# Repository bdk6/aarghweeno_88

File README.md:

# aarghweeno_88
An Arduino compatible prototyping board

Short story: add prototyping area to Arduino compatible AVR development board.

I have been a fan of the AVR processors for a long time.  My first project with them was in 2006.  The Arduino came along later and it is a neat system, making it very easy to get started.  When I say "Arduino" I mean AVR based ones.  If I should refer to some other, I'll specify.  

Now you can get an Aruino Nano clone for less than $5 US all over the web.  But one thing that has often bothered me about all the standard Arduino boards is that they don't have onbaord prototyping areas.  This little project aims to fix that.

The board is 3.9 x 3.9 inches, just under the 100 x 100 mm size of JLCPCBs cheapest PC board service.  About 1 1/2 inch along the "top" edge holds the AVR, regulator, programming header, and associated components.  The rest of the board is taken up with a prototyping area of holes on 0.1" centers arranged in groups of threes and long rows of bus connections.  There are also four mounting holes, another thing absent from standard Arduinos.  The idea is you can build an entire project on a single board without all those "dupont" (I hate that name) wires and whatnot crap going from board to board.

The one thing I left off that I agonized over was a USB interface or any type of serial port circuit.  Many of my projects don't need either and I generally prefer to use an AVR programmer to flash the chip.  If you really need/want a USB interface you can add it in the proto area.  You might need an SMD to DIP adapter or maybe just buy a USB to 5V serial module with 0.1" header pins.

You are welcome to use this board for any purpose, personal or commercial, as long as you leave the copyright notice in place.  I would like to know about any projects you build with it or comments in general.  If you make enough money selling it to hire Bill Gates and Jeff Bezos as your house boys, I wouldn't mind if you slipped me a mil or two.

20220807   First set of boards
I got the first boards back from JLCPCB on Thursday.  Friday morning I started soldering one up.  After replacing the LED that I soldered in backward, everthing seems to be working fine.  A bit more testing to do, but so far, so good.

Today I cleaned up some minor flaws and I'm releasing version 1.1.  Changed to value of C3 (to 0.1 uF from 0.33 uF) and cleaned up some silkscreen.  No substantive changes.  I plan to run a set of these once I've tested the first one more.

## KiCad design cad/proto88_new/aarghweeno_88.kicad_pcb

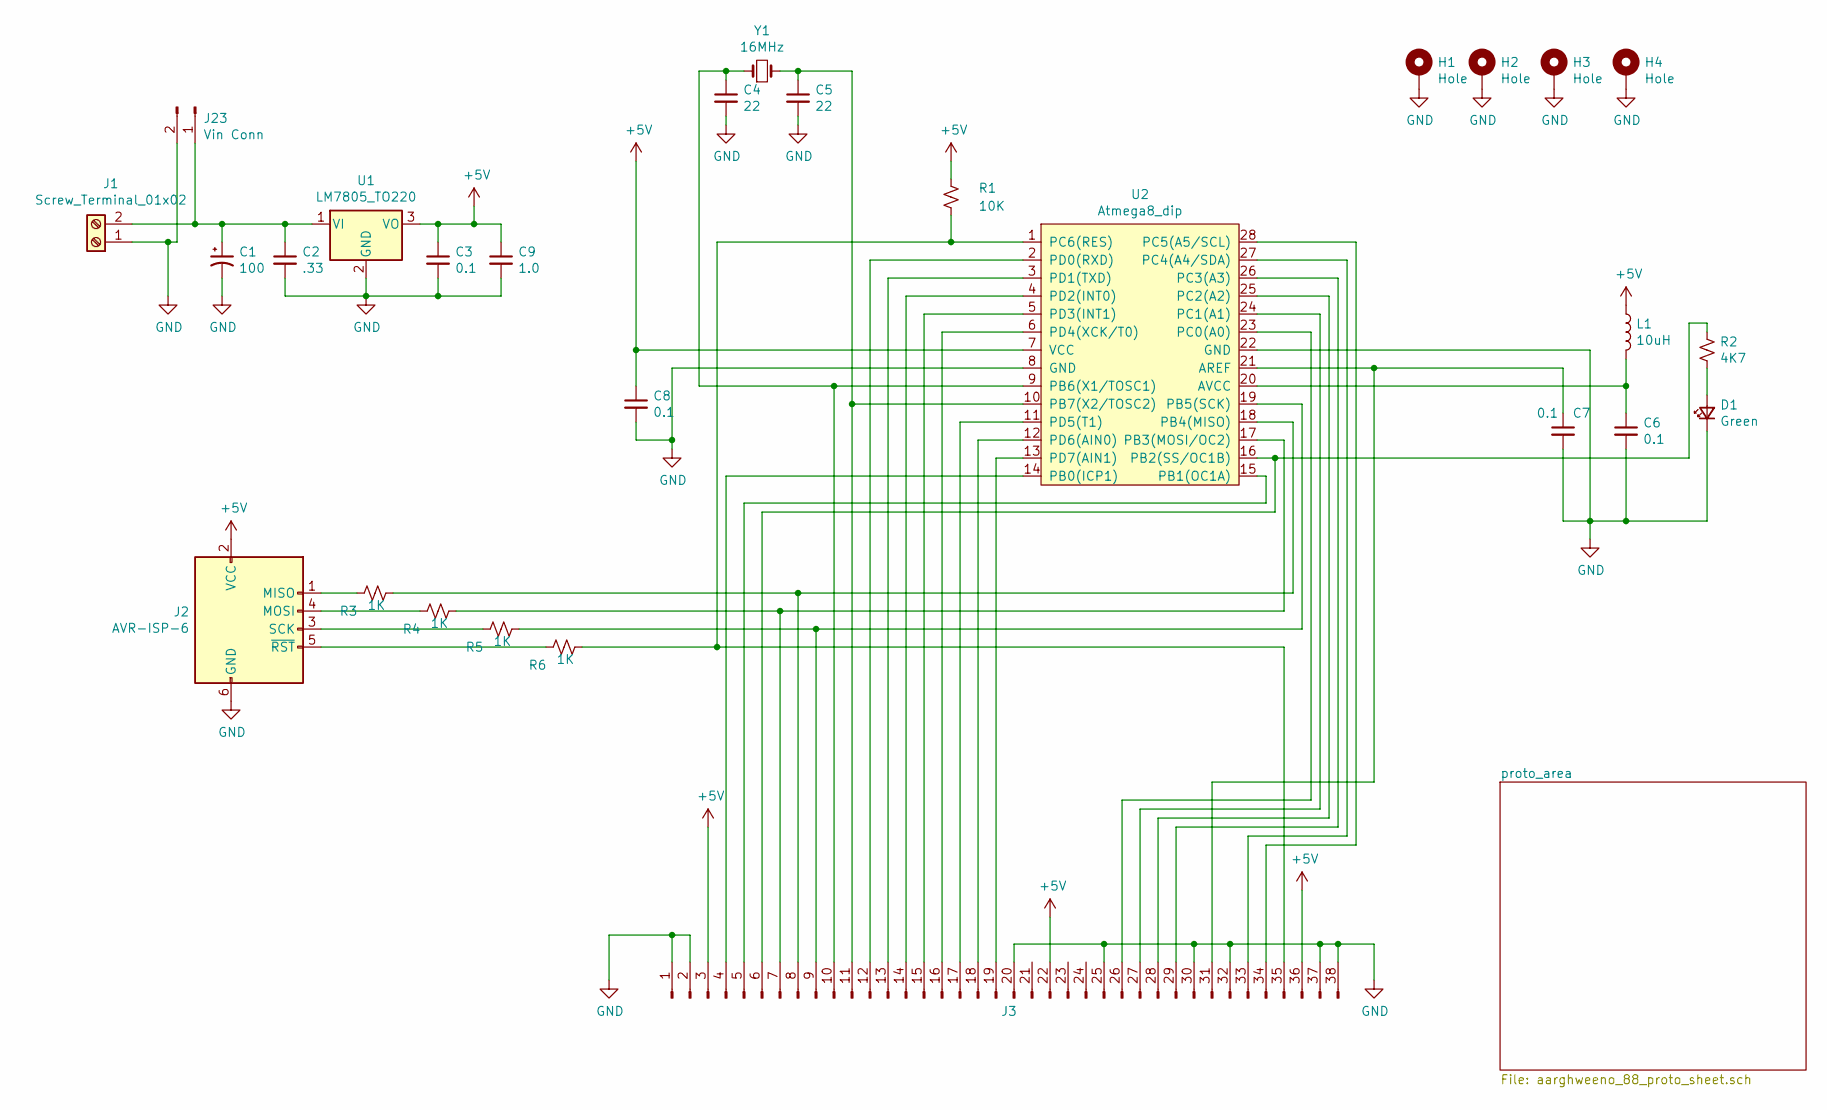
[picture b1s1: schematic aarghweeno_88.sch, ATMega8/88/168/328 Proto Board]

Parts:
C1: 100; CP_Radial_D8.0mm_P5.00mm
C2: .33; C_Disc_D5.0mm_W2.5mm_P5.00mm
C3, C6, C7, C8: 0.1; C_Disc_D5.0mm_W2.5mm_P5.00mm
C4, C5: 22; C_Disc_D5.0mm_W2.5mm_P5.00mm
C9: 1.0; C_Disc_D5.0mm_W2.5mm_P5.00mm
D1: Green; LED_D5.0mm
H1, H2, H3, H4: Hole; MountingHole_3.5mm_Pad
J1: Screw_Terminal_01x02; TerminalBlock_Altech_AK300-2_P5.00mm
J2: AVR-ISP-6; PinHeader_2x03_P2.54mm_Vertical
J3: Conn_01x38_Male; ProtoStrip_1x38_P2.54mm_Vertical
J23: Vin Conn; PinHeader_1x02_P2.54mm_Vertical
L1: 10uH; L_Axial_L9.5mm_D4.0mm_P12.70mm_Horizontal_Fastron_SMCC
R1: 10K; R_Axial_DIN0309_L9.0mm_D3.2mm_P12.70mm_Horizontal
R2: 4K7; R_Axial_DIN0309_L9.0mm_D3.2mm_P12.70mm_Horizontal
R3, R4, R5, R6: 1K; R_Axial_DIN0309_L9.0mm_D3.2mm_P12.70mm_Horizontal
U1: LM7805_TO220; TO-220-3_Vertical
U2: Atmega8_dip; DIP-28_W7.62mm_Socket_LongPads
Y1: 16MHz; Crystal_HC49-U_Vertical

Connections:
+5V: C3.1, C8.1, C9.1, J2.2 (VCC), J3.3, J3.22, J3.36, L1.1, R1.1, U1.3 (VO), U2.7 (VCC)
GND: C1.2, C2.2, C3.2, C4.2, C5.2, C6.2, C7.2, C8.2, C9.2, D1.1 (K), H1.1, H2.1, H3.1, H4.1, J1.1, J2.6 (GND), J3.1, J3.2, J3.20, J3.25, J3.30, J3.32, J3.37, J3.38, J23.2, U1.2 (GND), U2.8 (GND), U2.22 (GND)
unnamed: C1.1, C2.1, J1.2, J23.1, U1.1 (VI)
unnamed: C4.1, J3.10, U2.9 (PB6(X1/TOSC1)), Y1.1
unnamed: C5.1, J3.11, U2.10 (PB7(X2/TOSC2)), Y1.2
unnamed: C6.1, L1.2, U2.20 (AVCC)
unnamed: C7.1, J3.31, U2.21 (AREF)
unnamed: D1.2 (A), R2.2
unnamed: J2.1 (MISO), R3.2
unnamed: J2.3 (SCK), R5.2
unnamed: J2.4 (MOSI), R4.2
unnamed: J2.5 (~RST), R6.2
unnamed: J3.4, U2.14 (PB0(ICP1))
unnamed: J3.5, U2.15 (PB1(OC1A))
unnamed: J3.6, R2.1, U2.16 (PB2(SS/OC1B))
unnamed: J3.7, R4.1, U2.17 (PB3(MOSI/OC2))
unnamed: J3.8, R3.1, U2.18 (PB4(MISO))
unnamed: J3.9, R5.1, U2.19 (PB5(SCK))
unnamed: J3.12, U2.2 (PD0(RXD))
unnamed: J3.13, U2.3 (PD1(TXD))
unnamed: J3.14, U2.4 (PD2(INT0))
unnamed: J3.15, U2.5 (PD3(INT1))
unnamed: J3.16, U2.6 (PD4(XCK/T0))
unnamed: J3.17, U2.11 (PD5(T1))
unnamed: J3.18, U2.12 (PD6(AIN0))
unnamed: J3.19, U2.13 (PD7(AIN1))
unnamed: J3.26, U2.23 (PC0(A0))
unnamed: J3.27, U2.24 (PC1(A1))
unnamed: J3.28, U2.25 (PC2(A2))
unnamed: J3.29, U2.26 (PC3(A3))
unnamed: J3.33, U2.27 (PC4(A4/SDA))
unnamed: J3.34, U2.28 (PC5(A5/SCL))
unnamed: J3.35, R1.2, R6.1, U2.1 (PC6(RES))

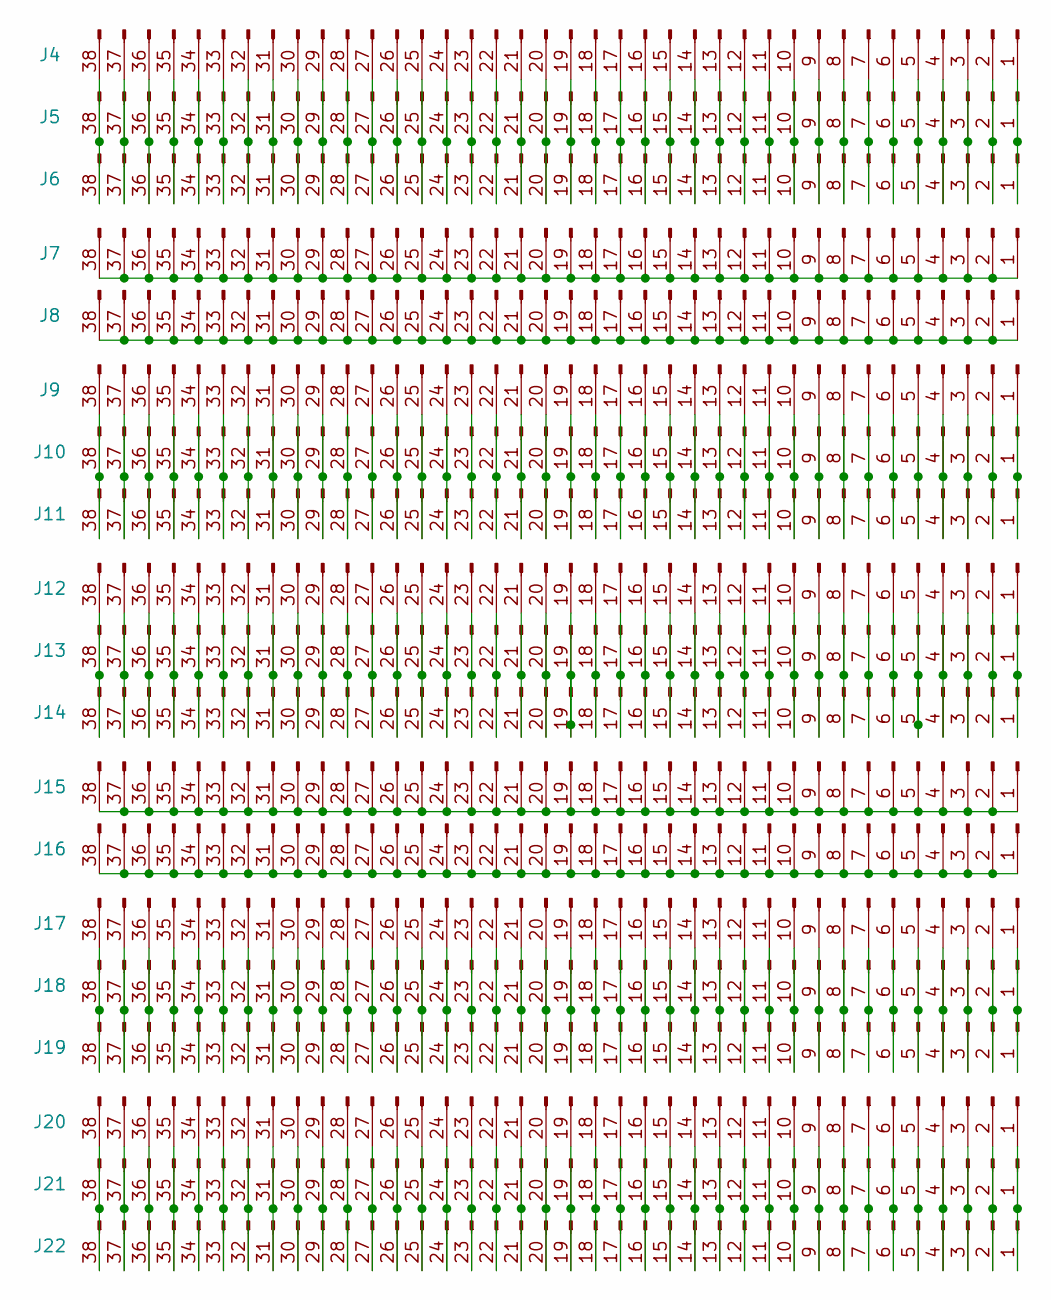
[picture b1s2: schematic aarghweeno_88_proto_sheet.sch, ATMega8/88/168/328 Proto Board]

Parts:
J4, J5, J6, J7, J8, J9, J10, J11, J12, J13, J14, J15, J16, J17, J18, J19, J20, J21, J22: Conn_01x38_Male; ProtoStrip_1x38_P2.54mm_Vertical

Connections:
unnamed: J4.1, J5.1, J6.1
unnamed: J4.2, J5.2, J6.2
unnamed: J4.3, J5.3, J6.3
unnamed: J4.4, J5.4, J6.4
unnamed: J4.5, J5.5, J6.5
unnamed: J4.6, J5.6, J6.6
unnamed: J4.7, J5.7, J6.7
unnamed: J4.8, J5.8, J6.8
unnamed: J4.9, J5.9, J6.9
unnamed: J4.10, J5.10, J6.10
unnamed: J4.11, J5.11, J6.11
unnamed: J4.12, J5.12, J6.12
unnamed: J4.13, J5.13, J6.13
unnamed: J4.14, J5.14, J6.14
unnamed: J4.15, J5.15, J6.15
unnamed: J4.16, J5.16, J6.16
unnamed: J4.17, J5.17, J6.17
unnamed: J4.18, J5.18, J6.18
unnamed: J4.19, J5.19, J6.19
unnamed: J4.20, J5.20, J6.20
unnamed: J4.21, J5.21, J6.21
unnamed: J4.22, J5.22, J6.22
unnamed: J4.23, J5.23, J6.23
unnamed: J4.24, J5.24, J6.24
unnamed: J4.25, J5.25, J6.25
unnamed: J4.26, J5.26, J6.26
unnamed: J4.27, J5.27, J6.27
unnamed: J4.28, J5.28, J6.28
unnamed: J4.29, J5.29, J6.29
unnamed: J4.30, J5.30, J6.30
unnamed: J4.31, J5.31, J6.31
unnamed: J4.32, J5.32, J6.32
unnamed: J4.33, J5.33, J6.33
unnamed: J4.34, J5.34, J6.34
unnamed: J4.35, J5.35, J6.35
unnamed: J4.36, J5.36, J6.36
unnamed: J4.37, J5.37, J6.37
unnamed: J4.38, J5.38, J6.38
unnamed: J7.1, J7.2, J7.3, J7.4, J7.5, J7.6, J7.7, J7.8, J7.9, J7.10, J7.11, J7.12, J7.13, J7.14, J7.15, J7.16, J7.17, J7.18, J7.19, J7.20, J7.21, J7.22, J7.23, J7.24, J7.25, J7.26, J7.27, J7.28, J7.29, J7.30, J7.31, J7.32, J7.33, J7.34, J7.35, J7.36, J7.37, J7.38
unnamed: J8.1, J8.2, J8.3, J8.4, J8.5, J8.6, J8.7, J8.8, J8.9, J8.10, J8.11, J8.12, J8.13, J8.14, J8.15, J8.16, J8.17, J8.18, J8.19, J8.20, J8.21, J8.22, J8.23, J8.24, J8.25, J8.26, J8.27, J8.28, J8.29, J8.30, J8.31, J8.32, J8.33, J8.34, J8.35, J8.36, J8.37, J8.38
unnamed: J9.1, J10.1, J11.1
unnamed: J9.2, J10.2, J11.2
unnamed: J9.3, J10.3, J11.3
unnamed: J9.4, J10.4, J11.4
unnamed: J9.5, J10.5, J11.5
unnamed: J9.6, J10.6, J11.6
unnamed: J9.7, J10.7, J11.7
unnamed: J9.8, J10.8, J11.8
unnamed: J9.9, J10.9, J11.9
unnamed: J9.10, J10.10, J11.10
unnamed: J9.11, J10.11, J11.11
unnamed: J9.12, J10.12, J11.12
unnamed: J9.13, J10.13, J11.13
unnamed: J9.14, J10.14, J11.14
unnamed: J9.15, J10.15, J11.15
unnamed: J9.16, J10.16, J11.16
unnamed: J9.17, J10.17, J11.17
unnamed: J9.18, J10.18, J11.18
unnamed: J9.19, J10.19, J11.19
unnamed: J9.20, J10.20, J11.20
unnamed: J9.21, J10.21, J11.21
unnamed: J9.22, J10.22, J11.22
unnamed: J9.23, J10.23, J11.23
unnamed: J9.24, J10.24, J11.24
unnamed: J9.25, J10.25, J11.25
unnamed: J9.26, J10.26, J11.26
unnamed: J9.27, J10.27, J11.27
unnamed: J9.28, J10.28, J11.28
unnamed: J9.29, J10.29, J11.29
unnamed: J9.30, J10.30, J11.30
unnamed: J9.31, J10.31, J11.31
unnamed: J9.32, J10.32, J11.32
unnamed: J9.33, J10.33, J11.33
unnamed: J9.34, J10.34, J11.34
unnamed: J9.35, J10.35, J11.35
unnamed: J9.36, J10.36, J11.36
unnamed: J9.37, J10.37, J11.37
unnamed: J9.38, J10.38, J11.38
unnamed: J12.1, J13.1, J14.1
unnamed: J12.2, J13.2, J14.2
unnamed: J12.3, J13.3, J14.3
unnamed: J12.4, J13.4, J14.4
unnamed: J12.5, J13.5, J14.5
unnamed: J12.6, J13.6, J14.6
unnamed: J12.7, J13.7, J14.7
unnamed: J12.8, J13.8, J14.8
unnamed: J12.9, J13.9, J14.9
unnamed: J12.10, J13.10, J14.10
unnamed: J12.11, J13.11, J14.11
unnamed: J12.12, J13.12, J14.12
unnamed: J12.13, J13.13, J14.13
unnamed: J12.14, J13.14, J14.14
unnamed: J12.15, J13.15, J14.15
unnamed: J12.16, J13.16, J14.16
unnamed: J12.17, J13.17, J14.17
unnamed: J12.18, J13.18, J14.18
unnamed: J12.19, J13.19, J14.19
unnamed: J12.20, J13.20, J14.20
unnamed: J12.21, J13.21, J14.21
unnamed: J12.22, J13.22, J14.22
unnamed: J12.23, J13.23, J14.23
unnamed: J12.24, J13.24, J14.24
unnamed: J12.25, J13.25, J14.25
unnamed: J12.26, J13.26, J14.26
unnamed: J12.27, J13.27, J14.27
unnamed: J12.28, J13.28, J14.28
unnamed: J12.29, J13.29, J14.29
unnamed: J12.30, J13.30, J14.30
unnamed: J12.31, J13.31, J14.31
unnamed: J12.32, J13.32, J14.32
unnamed: J12.33, J13.33, J14.33
unnamed: J12.34, J13.34, J14.34
unnamed: J12.35, J13.35, J14.35
unnamed: J12.36, J13.36, J14.36
unnamed: J12.37, J13.37, J14.37
unnamed: J12.38, J13.38, J14.38
unnamed: J15.1, J15.2, J15.3, J15.4, J15.5, J15.6, J15.7, J15.8, J15.9, J15.10, J15.11, J15.12, J15.13, J15.14, J15.15, J15.16, J15.17, J15.18, J15.19, J15.20, J15.21, J15.22, J15.23, J15.24, J15.25, J15.26, J15.27, J15.28, J15.29, J15.30, J15.31, J15.32, J15.33, J15.34, J15.35, J15.36, J15.37, J15.38
unnamed: J16.1, J16.2, J16.3, J16.4, J16.5, J16.6, J16.7, J16.8, J16.9, J16.10, J16.11, J16.12, J16.13, J16.14, J16.15, J16.16, J16.17, J16.18, J16.19, J16.20, J16.21, J16.22, J16.23, J16.24, J16.25, J16.26, J16.27, J16.28, J16.29, J16.30, J16.31, J16.32, J16.33, J16.34, J16.35, J16.36, J16.37, J16.38
unnamed: J17.1, J18.1, J19.1
unnamed: J17.2, J18.2, J19.2
unnamed: J17.3, J18.3, J19.3
unnamed: J17.4, J18.4, J19.4
unnamed: J17.5, J18.5, J19.5
unnamed: J17.6, J18.6, J19.6
unnamed: J17.7, J18.7, J19.7
unnamed: J17.8, J18.8, J19.8
unnamed: J17.9, J18.9, J19.9
unnamed: J17.10, J18.10, J19.10
unnamed: J17.11, J18.11, J19.11
unnamed: J17.12, J18.12, J19.12
unnamed: J17.13, J18.13, J19.13
unnamed: J17.14, J18.14, J19.14
unnamed: J17.15, J18.15, J19.15
unnamed: J17.16, J18.16, J19.16
unnamed: J17.17, J18.17, J19.17
unnamed: J17.18, J18.18, J19.18
unnamed: J17.19, J18.19, J19.19
unnamed: J17.20, J18.20, J19.20
unnamed: J17.21, J18.21, J19.21
unnamed: J17.22, J18.22, J19.22
unnamed: J17.23, J18.23, J19.23
unnamed: J17.24, J18.24, J19.24
unnamed: J17.25, J18.25, J19.25
unnamed: J17.26, J18.26, J19.26
unnamed: J17.27, J18.27, J19.27
unnamed: J17.28, J18.28, J19.28
unnamed: J17.29, J18.29, J19.29
unnamed: J17.30, J18.30, J19.30
unnamed: J17.31, J18.31, J19.31
unnamed: J17.32, J18.32, J19.32
unnamed: J17.33, J18.33, J19.33
unnamed: J17.34, J18.34, J19.34
unnamed: J17.35, J18.35, J19.35
unnamed: J17.36, J18.36, J19.36
unnamed: J17.37, J18.37, J19.37
unnamed: J17.38, J18.38, J19.38
unnamed: J20.1, J21.1, J22.1
unnamed: J20.2, J21.2, J22.2
unnamed: J20.3, J21.3, J22.3
unnamed: J20.4, J21.4, J22.4
unnamed: J20.5, J21.5, J22.5
unnamed: J20.6, J21.6, J22.6
unnamed: J20.7, J21.7, J22.7
unnamed: J20.8, J21.8, J22.8
unnamed: J20.9, J21.9, J22.9
unnamed: J20.10, J21.10, J22.10
unnamed: J20.11, J21.11, J22.11
unnamed: J20.12, J21.12, J22.12
unnamed: J20.13, J21.13, J22.13
unnamed: J20.14, J21.14, J22.14
unnamed: J20.15, J21.15, J22.15
unnamed: J20.16, J21.16, J22.16
unnamed: J20.17, J21.17, J22.17
unnamed: J20.18, J21.18, J22.18
unnamed: J20.19, J21.19, J22.19
unnamed: J20.20, J21.20, J22.20
unnamed: J20.21, J21.21, J22.21
unnamed: J20.22, J21.22, J22.22
unnamed: J20.23, J21.23, J22.23
unnamed: J20.24, J21.24, J22.24
unnamed: J20.25, J21.25, J22.25
unnamed: J20.26, J21.26, J22.26
unnamed: J20.27, J21.27, J22.27
unnamed: J20.28, J21.28, J22.28
unnamed: J20.29, J21.29, J22.29
unnamed: J20.30, J21.30, J22.30
unnamed: J20.31, J21.31, J22.31
unnamed: J20.32, J21.32, J22.32
unnamed: J20.33, J21.33, J22.33
unnamed: J20.34, J21.34, J22.34
unnamed: J20.35, J21.35, J22.35
unnamed: J20.36, J21.36, J22.36
unnamed: J20.37, J21.37, J22.37
unnamed: J20.38, J21.38, J22.38

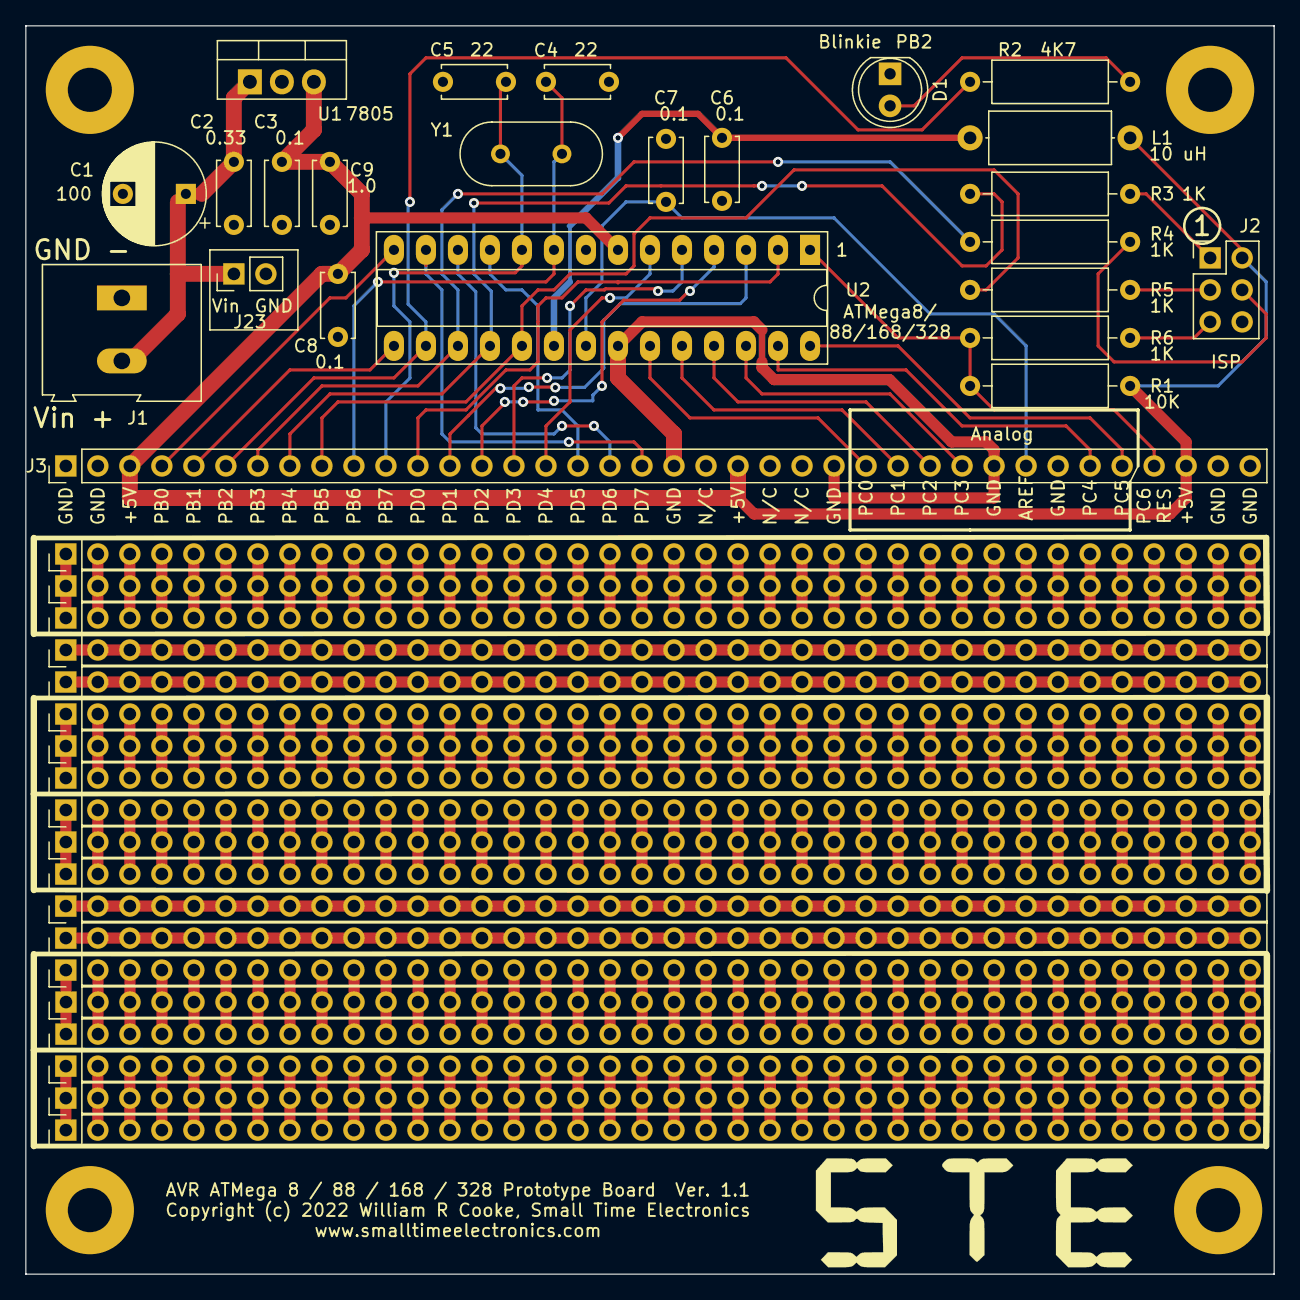
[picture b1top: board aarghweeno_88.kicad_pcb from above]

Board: 2 copper layers, 99.1 x 99.1 mm, 47 parts (0 on the bottom side), 227 nets.

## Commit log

2022-07-21 Schematic and PCB nearly complete for ver 0.1
2022-07-21 Release Candidate 1 ver 1.0
2022-07-21 Moved files around
2022-07-21 Created Gerbers and zip for manufacture.
2022-08-07 Changed reg cap value, changed version, added port# to LED, cleaned up silkscreen.
2022-08-07 Removed old files
2022-08-09 Added user doc.

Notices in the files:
cad/proto88_new/aarghweeno_88.kicad_pcb:
Copyright (c) 2022 William R Cooke, Small Time Electronics
